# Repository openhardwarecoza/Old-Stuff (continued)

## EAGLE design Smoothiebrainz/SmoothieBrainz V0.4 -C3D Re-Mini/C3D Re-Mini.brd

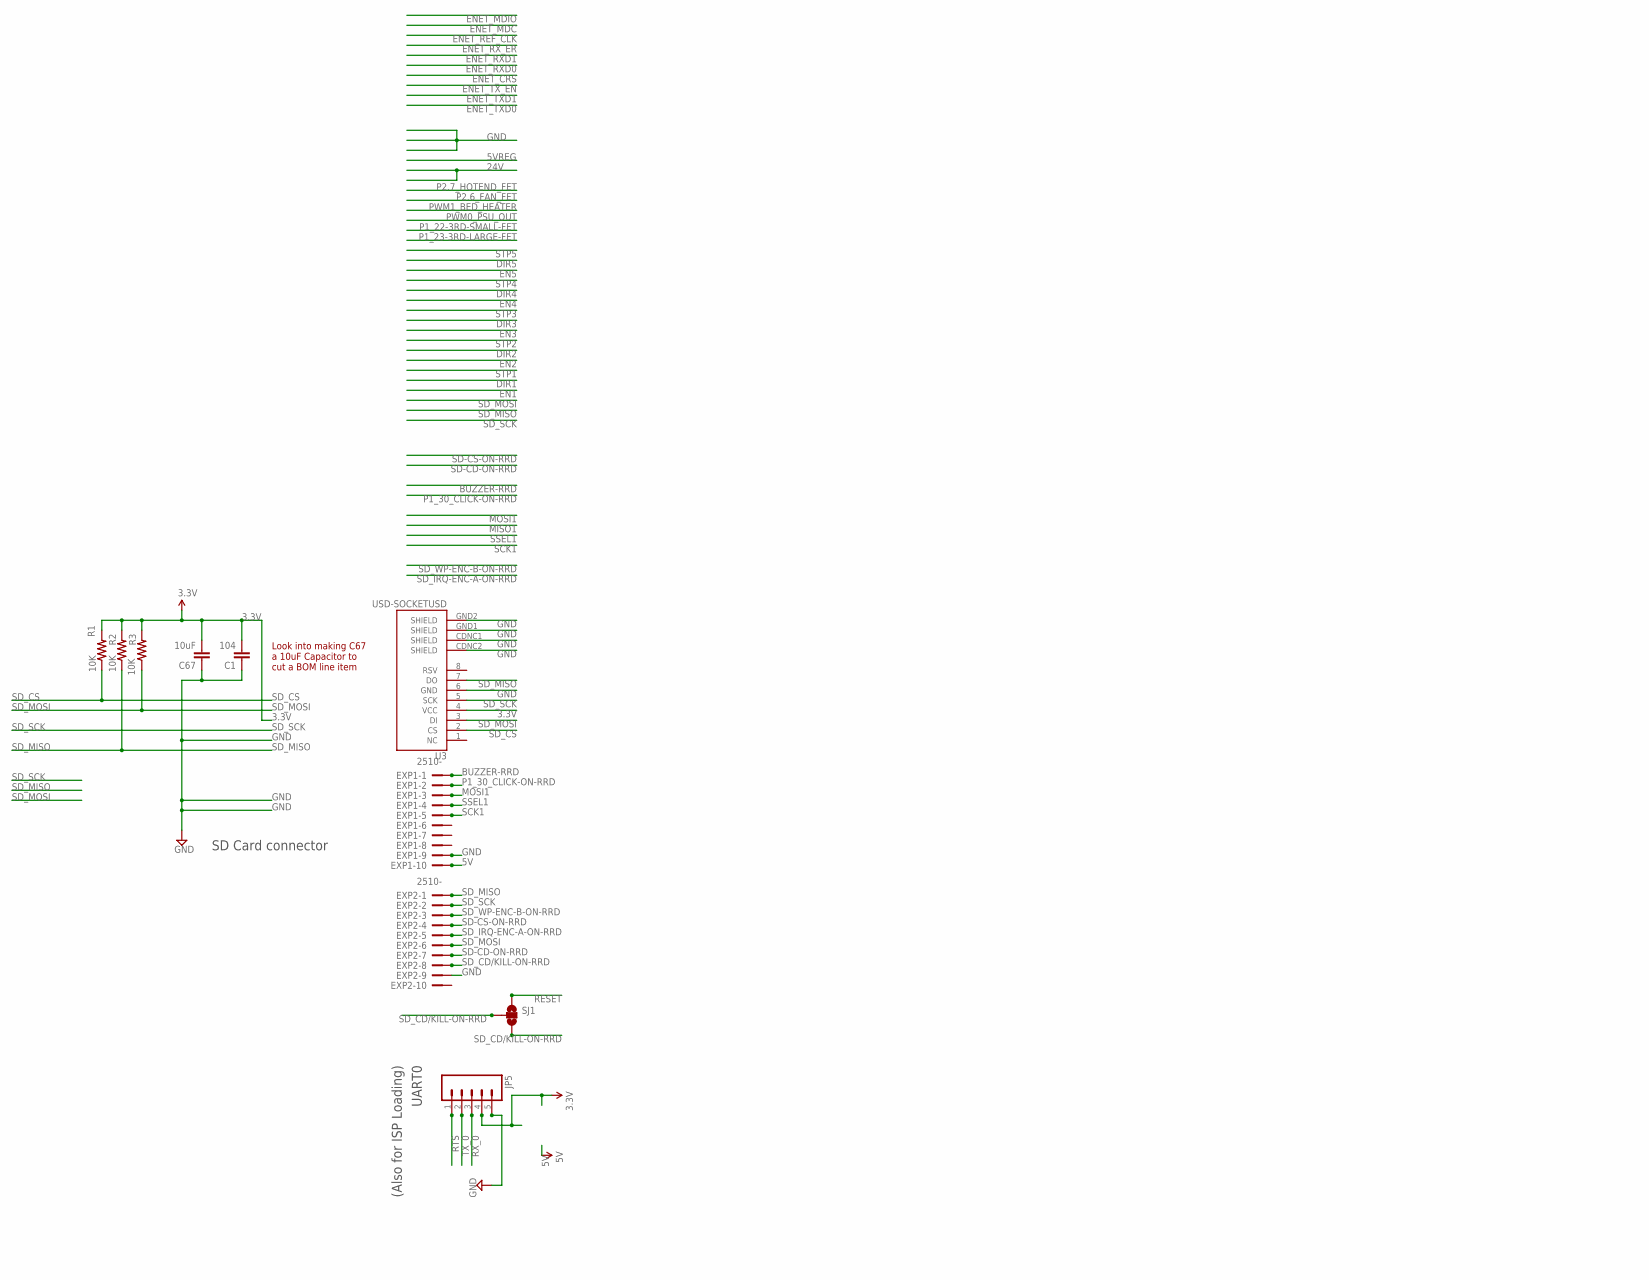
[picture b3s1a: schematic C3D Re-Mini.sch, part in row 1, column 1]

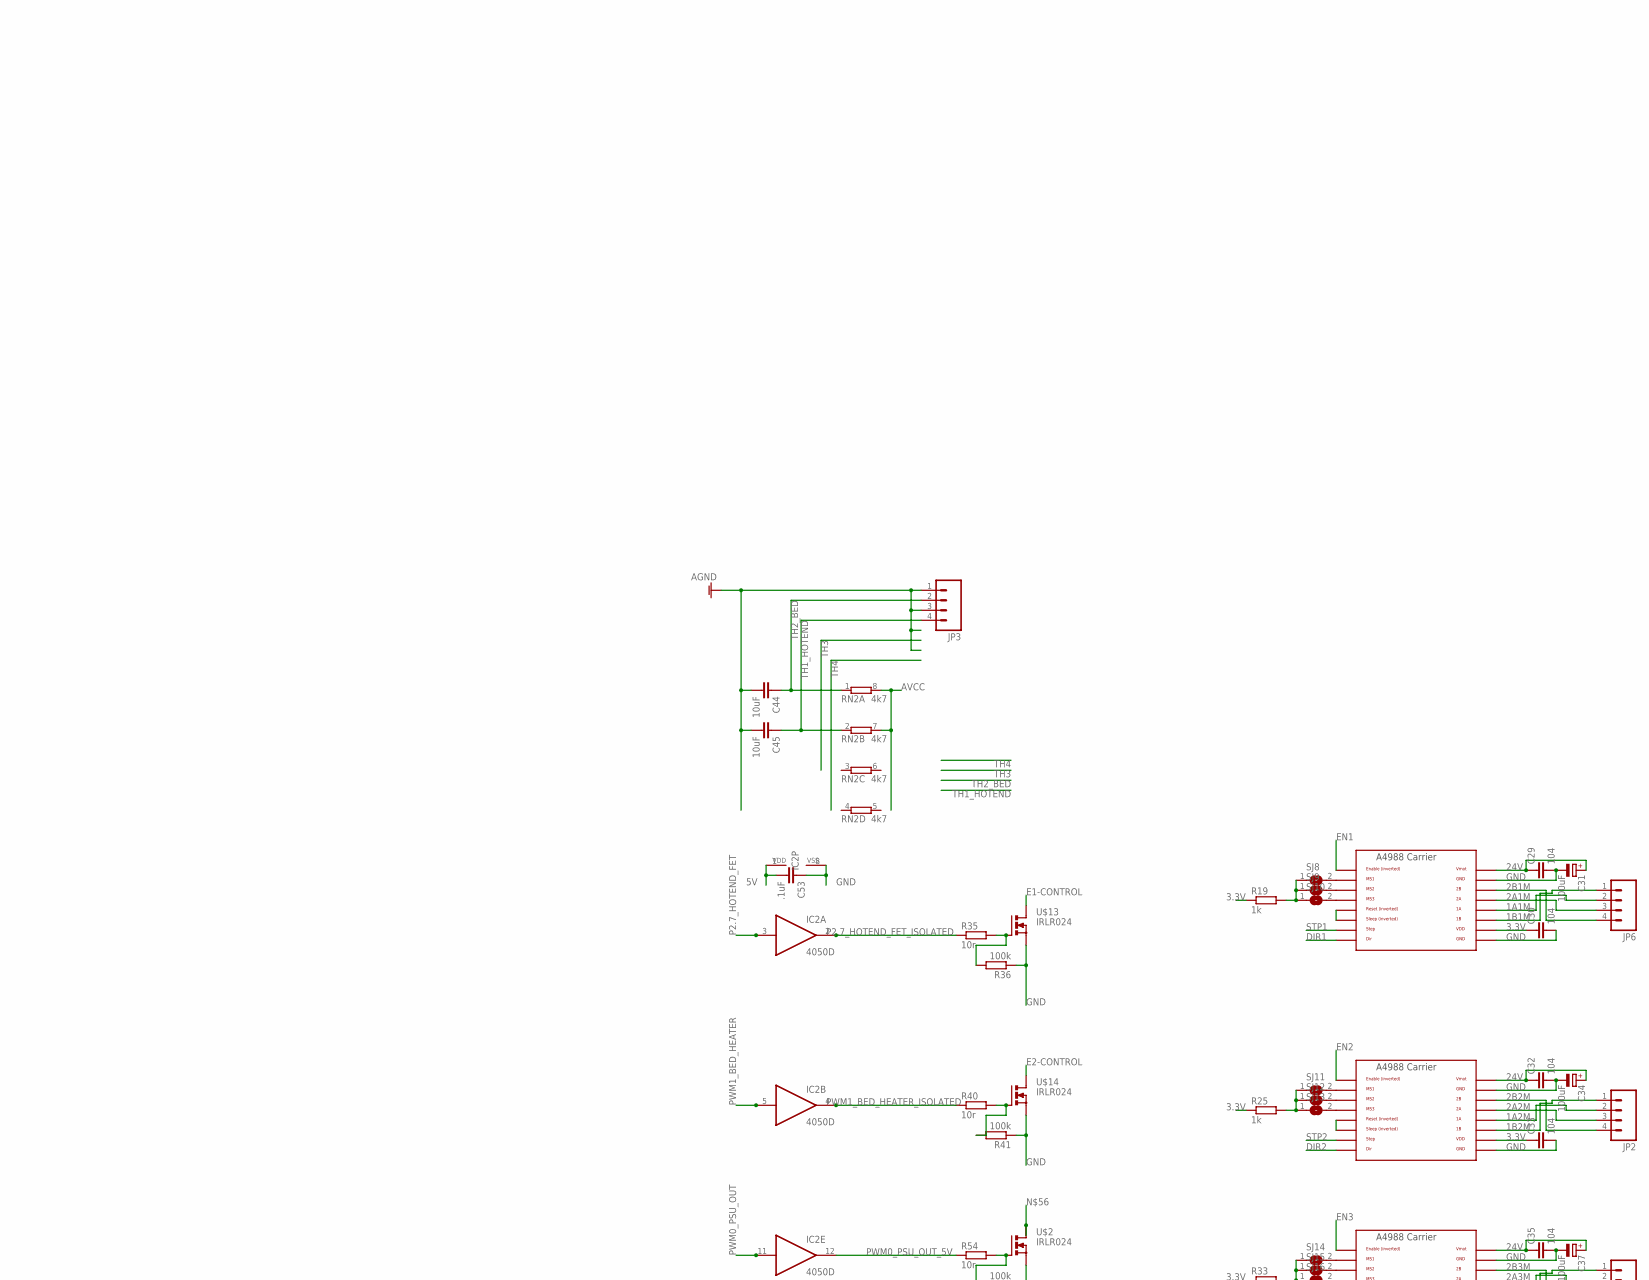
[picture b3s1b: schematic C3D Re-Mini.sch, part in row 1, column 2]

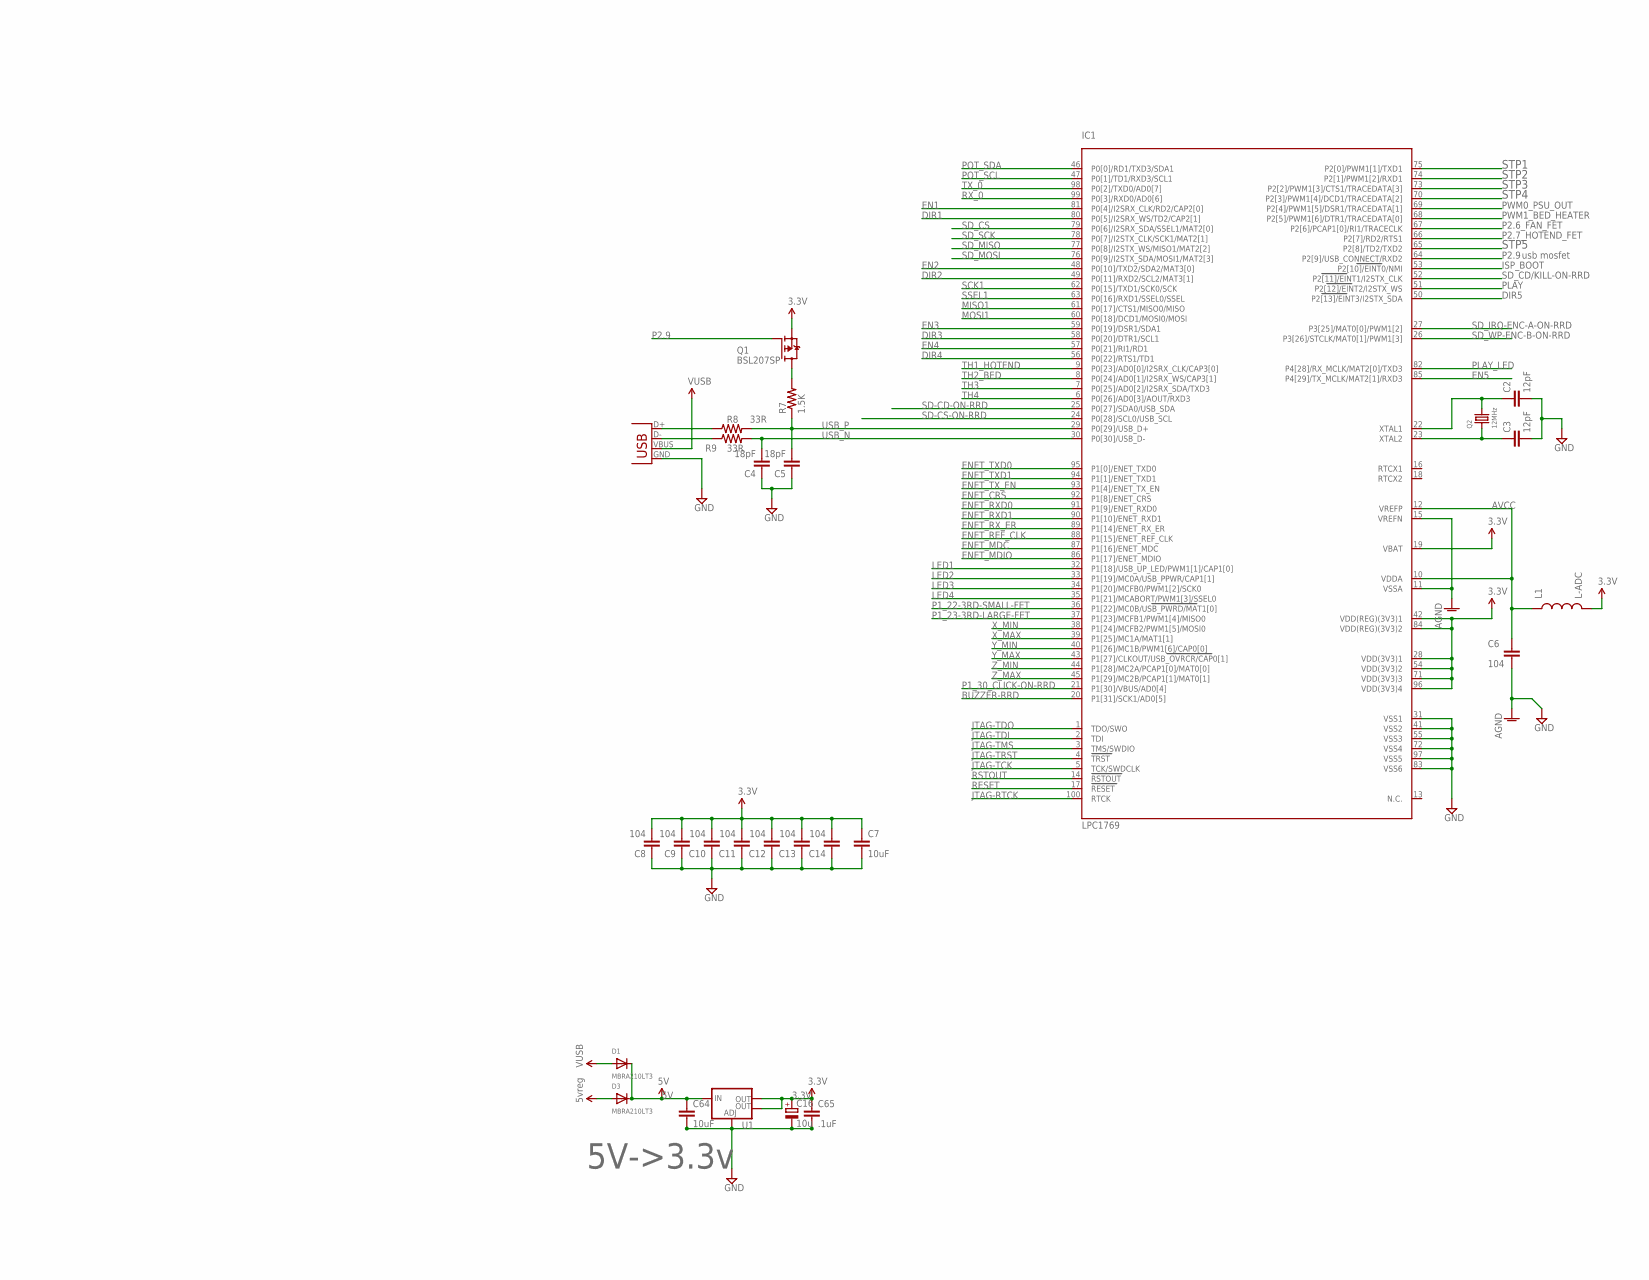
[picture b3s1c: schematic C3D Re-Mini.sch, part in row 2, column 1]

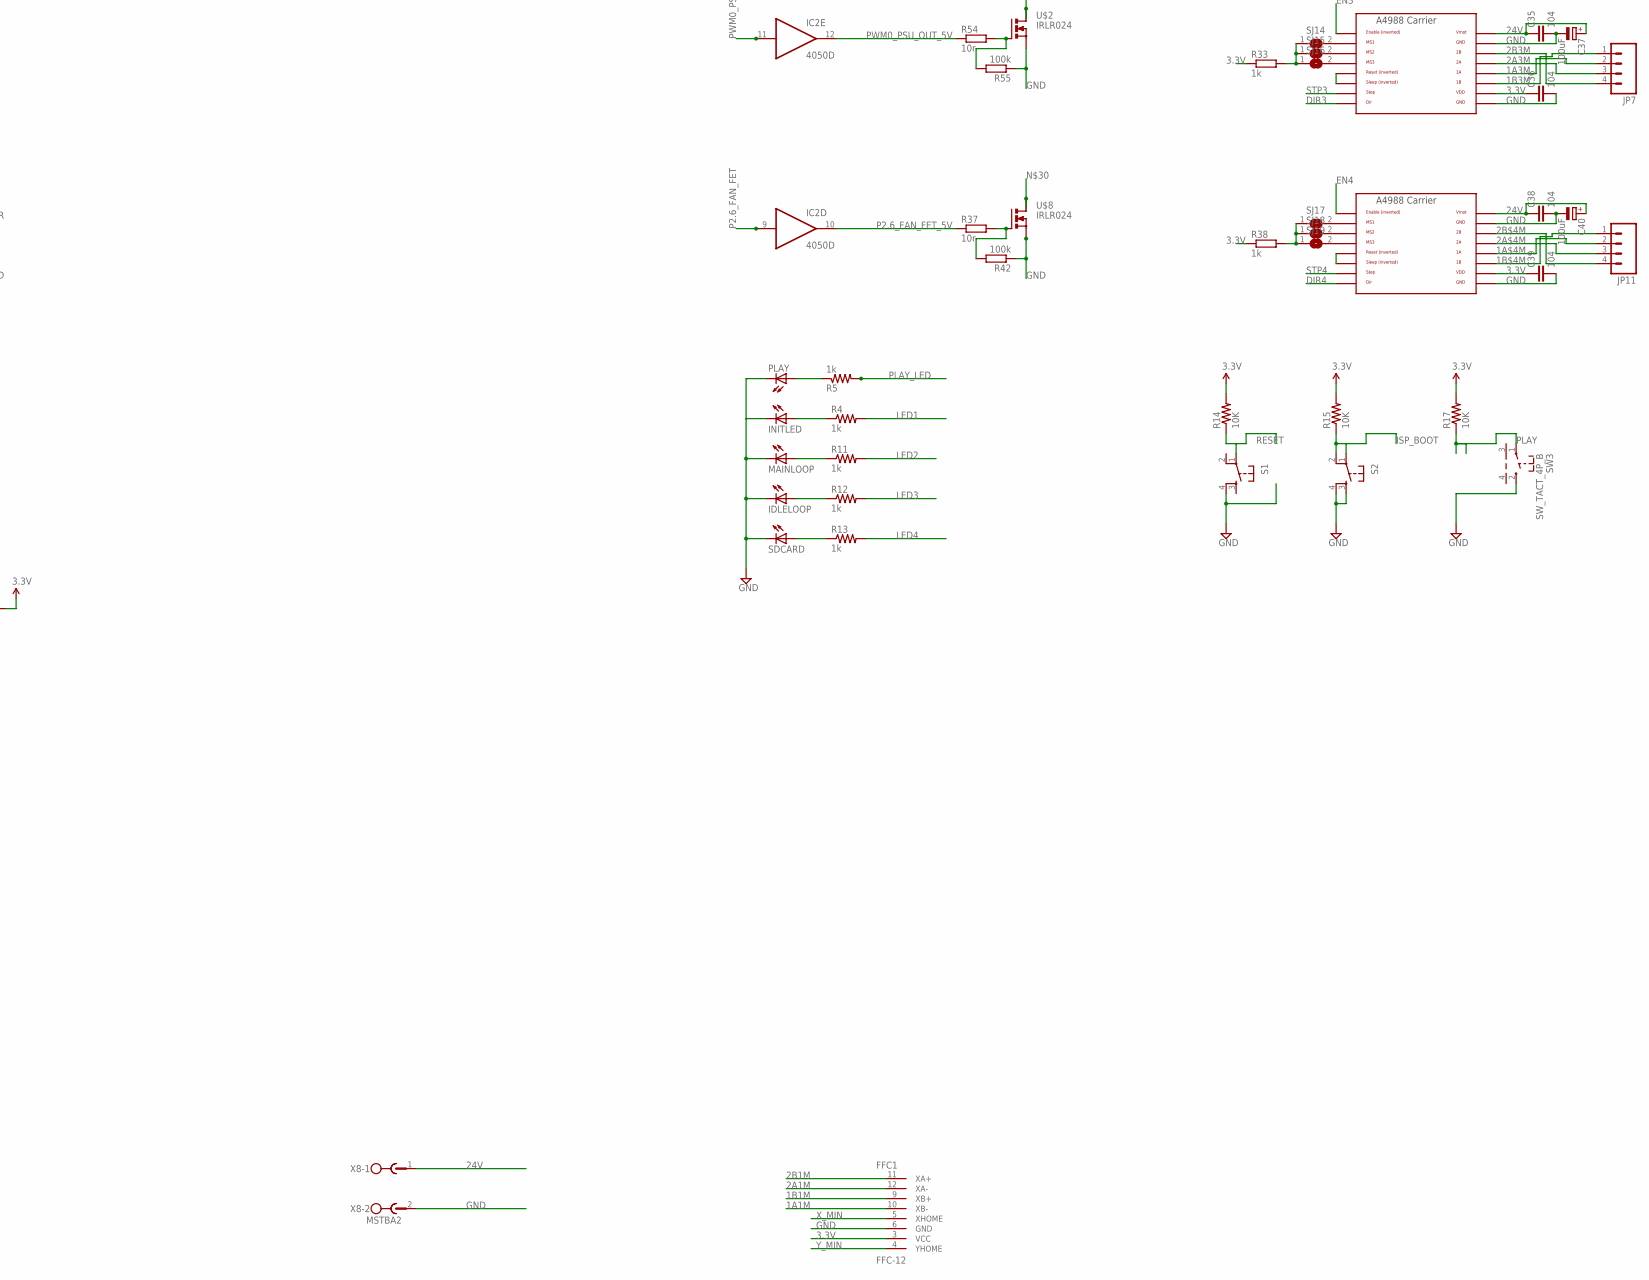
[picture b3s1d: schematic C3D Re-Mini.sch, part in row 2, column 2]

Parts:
C1, C6, C8, C9, C10, C11, C12, C13, C14, C29, C30, C32, C33, C35, C36, C38, C39: 104; C0603
C2, C3: 12pF; C0603
C4, C5: 18pF; C0603
C7, C44, C45, C67: 10uF; C0603
C16: 10u; E2-4
C31, C34, C37, C40: 100uF; 153CLV-0807
C53, C65: .1uF; C0603
C64: 10uF; C1206
D1, D3: MBRA210LT3; SMADIODE
EXP1, EXP2: 2510-; PAK100/2500-10
FFC1: FFC-12; FFC
IC1: LPC1769; LQFP100
IC2: 4050D; SO16
IDLELOOP: LEDCHIP-LED0805; CHIP-LED0805
INITLED: LEDCHIP-LED0805; CHIP-LED0805
JP2, JP6, JP7, JP11: M04POLAR_LOCK; MOLEX-1X4_LOCK
JP3: M04LOCK; 1X04_LOCK
JP5: M05NO_SILK; 1X05_NO_SILK
L1: L-ADC; 0603
MAINLOOP: LEDCHIP-LED0805; CHIP-LED0805
PLAY: LEDCHIP-LED0805; CHIP-LED0805
Q1: BSL207SP; SC74_INFINEON
Q2: 12MHz; CRYSTAL_3.2X2.5
R1, R2, R3, R14, R15, R17: 10K; R0603
R4, R5, R11, R12, R13: 1k; R0603
R7: 1.5K; R0603
R8, R9: 33R; R0603
R19, R25, R33, R38: 1k; R0603@1
R35, R37, R40, R54: 10r; R0603@1
R36, R41, R42, R55: 100k; R0603@1
RN2: 4k7; 0603-ARV
S1, S2: TAC_SWITCHSMD; TACTILE_SWITCH_SMD
SDCARD: LEDCHIP-LED0805; CHIP-LED0805
SJ1: SOLDERJUMPER_2WAYS; SJ_3
SJ8, SJ9, SJ10, SJ11, SJ12, SJ13, SJ14, SJ15, SJ16, SJ17, SJ18, SJ19: SJ
SW3: SW_TACT_4P_B; SW_TACT_STANDARD_RIGHT_ANGLE
U1: V_REG_LM1117SOT223; SOT223
U3: USD-SOCKETUSD; USD-SOCKET-PP
U$1, U$5, U$6, U$7: POLOLU_A4983CARRIER; A4988BREAKOUT
U$2, U$8, U$13, U$14: IRLR024; D-PAK_TO252AA
X8: MSTBA2
X14: USBPTH; USB-B-PTH

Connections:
1A1M: FFC1.10 (XB-), JP6.2, U$1.1A
1A2M: JP2.2, U$5.1A
1A3M: JP7.2, U$6.1A
1A$4M: JP11.2, U$7.1A
1B1M: FFC1.9 (XB+), JP6.1, U$1.1B
1B2M: JP2.1, U$5.1B
1B3M: JP7.1, U$6.1B
1B$4M: JP11.1, U$7.1B
2A1M: FFC1.12 (XA-), JP6.3, U$1.2A
2A2M: JP2.3, U$5.2A
2A3M: JP7.3, U$6.2A
2A$4M: JP11.3, U$7.2A
2B1M: FFC1.11 (XA+), JP6.4, U$1.2B
2B2M: JP2.4, U$5.2B
2B3M: JP7.4, U$6.2B
2B$4M: JP11.4, U$7.2B
3.3V: C1.2, C7.1, C8.2, C9.2, C10.2, C11.2, C12.2, C13.2, C14.2, C16.+, C30.1, C33.1, C36.1, C39.1, C65.1, C67.2, FFC1.3 (VCC), IC1.19 (VBAT), IC1.28 (VDD(3V3)1), IC1.42 (VDD(REG)(3V3)1), IC1.54 (VDD(3V3)2), IC1.71 (VDD(3V3)3), IC1.84 (VDD(REG)(3V3)2), IC1.96 (VDD(3V3)4), JP5.4, L1.2, Q1.4 (S), R1.2, R2.2, R3.2, R14.2, R15.2, R17.2, R19.1, R25.1, R33.1, R38.1, U1.2 (OUT), U1.4 (OUT), U3.4 (VCC), U$1.VDD, U$5.VDD, U$6.VDD, U$7.VDD
5V: C53.2, C64.1, D1.C, D3.C, EXP1.10, IC2.1 (VDD), U1.3 (IN)
5VREG: D3.A
24V: C29.1, C31.+, C32.1, C34.+, C35.1, C37.+, C38.1, C40.+, U$1.VMOT, U$5.VMOT, U$6.VMOT, U$7.VMOT, X8.1
AGND: C6.2, C44.2, C45.2, IC1.11 (VSSA), IC1.15 (VREFN), JP3.1, JP3.3
AVCC: C6.1, IC1.10 (VDDA), IC1.12 (VREFP), L1.1, RN2.7 (2), RN2.8 (2)
BUZZER-RRD: EXP1.1, IC1.20 (P1[31]/SCK1/AD0[5])
DIR1: IC1.80 (P0[5]/I2SRX_WS/TD2/CAP2[1]), U$1.DIR
DIR2: IC1.49 (P0[11]/RXD2/SCL2/MAT3[1]), U$5.DIR
DIR3: IC1.58 (P0[20]/DTR1/SCL1), U$6.DIR
DIR4: IC1.56 (P0[22]/RTS1/TD1), U$7.DIR
DIR5: IC1.50 (P2[13]/EINT3/I2STX_SDA)
E1-CONTROL: U$13.4 (D)
E2-CONTROL: U$14.4 (D)
EN1: IC1.81 (P0[4]/I2SRX_CLK/RD2/CAP2[0]), U$1.EN
EN2: IC1.48 (P0[10]/TXD2/SDA2/MAT3[0]), U$5.EN
EN3: IC1.59 (P0[19]/DSR1/SDA1), U$6.EN
EN4: IC1.57 (P0[21]/RI1/RD1), U$7.EN
EN5: IC1.85 (P4[29]/TX_MCLK/MAT2[1]/RXD3)
ENET_CRS: IC1.92 (P1[8]/ENET_CRS)
ENET_MDC: IC1.87 (P1[16]/ENET_MDC)
ENET_MDIO: IC1.86 (P1[17]/ENET_MDIO)
ENET_REF_CLK: IC1.88 (P1[15]/ENET_REF_CLK)
ENET_RXD0: IC1.91 (P1[9]/ENET_RXD0)
ENET_RXD1: IC1.90 (P1[10]/ENET_RXD1)
ENET_RX_ER: IC1.89 (P1[14]/ENET_RX_ER)
ENET_TXD0: IC1.95 (P1[0]/ENET_TXD0)
ENET_TXD1: IC1.94 (P1[1]/ENET_TXD1)
ENET_TX_EN: IC1.93 (P1[4]/ENET_TX_EN)
GND: C1.1, C2.2, C3.2, C4.1, C5.1, C7.2, C8.1, C9.1, C10.1, C11.1, C12.1, C13.1, C14.1, C16.-, C29.2, C30.2, C31.-, C32.2, C33.2, C34.-, C35.2, C36.2, C37.-, C38.2, C39.2, C40.-, C53.1, C64.2, C65.2, C67.1, EXP1.9, EXP2.9, FFC1.6 (GND), IC1.31 (VSS1), IC1.41 (VSS2), IC1.55 (VSS3), IC1.72 (VSS4), IC1.83 (VSS6), IC1.97 (VSS5), IC2.8 (VSS), IDLELOOP.C, INITLED.C, JP5.5, MAINLOOP.C, PLAY.C, R36.1, R41.1, R42.1, R55.1, S1.4, S2.3, S2.4, SDCARD.C, SW3.2, U1.1 (ADJ), U3.6 (GND), U3.CDNC1 (SHIELD), U3.CDNC2 (SHIELD), U3.GND1 (SHIELD), U3.GND2 (SHIELD), U$1.GND, U$1.GND@0 (GND), U$2.3 (S), U$5.GND, U$5.GND@0 (GND), U$6.GND, U$6.GND@0 (GND), U$7.GND, U$7.GND@0 (GND), U$8.3 (S), U$13.3 (S), U$14.3 (S), X8.2, X14.GND
ISP_BOOT: IC1.53 (P2[10]/EINT0/NMI), R15.1, S2.1, S2.2
JTAG-RTCK: IC1.100 (RTCK)
JTAG-TCK: IC1.5 (TCK/SWDCLK)
JTAG-TDI: IC1.2 (TDI)
JTAG-TDO: IC1.1 (TDO/SWO)
JTAG-TMS: IC1.3 (TMS/SWDIO)
JTAG-TRST: IC1.4 (TRST)
LED1: IC1.32 (P1[18]/USB_UP_LED/PWM1[1]/CAP1[0]), R4.2
LED2: IC1.33 (P1[19]/MC0A/USB_PPWR/CAP1[1]), R11.2
LED3: IC1.34 (P1[20]/MCFB0/PWM1[2]/SCK0), R12.2
LED4: IC1.35 (P1[21]/MCABORT/PWM1[3]/SSEL0), R13.2
MISO1: IC1.61 (P0[17]/CTS1/MISO0/MISO)
MOSI1: EXP1.3, IC1.60 (P0[18]/DCD1/MOSI0/MOSI)
unnamed: C2.1, IC1.22 (XTAL1), Q2.2
unnamed: C3.1, IC1.23 (XTAL2), Q2.1
unnamed: PLAY.A, R5.1
unnamed: SJ8.2, U$1.MS1
unnamed: SJ9.2, U$1.MS2
unnamed: SJ10.2, U$1.MS3
unnamed: U$5.RST, U$5.SLP (SLEEP)
unnamed: R25.2, SJ11.1, SJ12.1, SJ13.1
unnamed: SJ11.2, U$5.MS1
unnamed: SJ12.2, U$5.MS2
unnamed: SJ13.2, U$5.MS3
unnamed: U$6.RST, U$6.SLP (SLEEP)
unnamed: R37.2, R42.2, U$8.1 (G)
unnamed: R33.2, SJ14.1, SJ15.1, SJ16.1
unnamed: SJ14.2, U$6.MS1
unnamed: SJ15.2, U$6.MS2
unnamed: SJ16.2, U$6.MS3
unnamed: R35.2, R36.2, U$13.1 (G)
unnamed: R19.2, SJ8.1, SJ9.1, SJ10.1
unnamed: U$7.RST, U$7.SLP (SLEEP)
unnamed: R38.2, SJ17.1, SJ18.1, SJ19.1
unnamed: SJ17.2, U$7.MS1
unnamed: SJ18.2, U$7.MS2
unnamed: U$1.RST, U$1.SLP (SLEEP)
unnamed: SJ19.2, U$7.MS3
unnamed: R40.2, R41.2, U$14.1 (G)
unnamed: Q1.1 (D), Q1.2 (D), Q1.5 (D), Q1.6 (D), R7.2
unnamed: R54.2, R55.2, U$2.1 (G)
unnamed: R8.1, X14.D+
unnamed: R9.1, X14.D-
unnamed: R13.1, SDCARD.A
unnamed: IDLELOOP.A, R12.1
unnamed: MAINLOOP.A, R11.1
unnamed: INITLED.A, R4.1
P1_22-3RD-SMALL-FET: IC1.36 (P1[22]/MC0B/USB_PWRD/MAT1[0])
P1_23-3RD-LARGE-FET: IC1.37 (P1[23]/MCFB1/PWM1[4]/MISO0)
P1_30_CLICK-ON-RRD: EXP1.2, IC1.21 (P1[30]/VBUS/AD0[4])
P2.6_FAN_FET: IC1.67 (P2[6]/PCAP1[0]/RI1/TRACECLK), IC2.9 (I)
P2.6_FAN_FET_5V: IC2.10 (O), R37.1
P2.7_HOTEND_FET: IC1.66 (P2[7]/RD2/RTS1), IC2.3 (I)
P2.7_HOTEND_FET_ISOLATED: IC2.2 (O), R35.1
P2.9: IC1.64 (P2[9]/USB_CONNECT/RXD2), Q1.3 (G)
PLAY: IC1.51 (P2[12]/EINT2/I2STX_WS), R17.1, SW3.1
PLAY_LED: IC1.82 (P4[28]/RX_MCLK/MAT2[0]/TXD3), R5.2
POT_SCL: IC1.47 (P0[1]/TD1/RXD3/SCL1)
POT_SDA: IC1.46 (P0[0]/RD1/TXD3/SDA1)
PWM0_PSU_OUT: IC1.69 (P2[4]/PWM1[5]/DSR1/TRACEDATA[1]), IC2.11 (I)
PWM0_PSU_OUT_5V: IC2.12 (O), R54.1
PWM1_BED_HEATER: IC1.68 (P2[5]/PWM1[6]/DTR1/TRACEDATA[0]), IC2.5 (I)
PWM1_BED_HEATER_ISOLATED: IC2.4 (O), R40.1
RESET: IC1.17 (RESET), R14.1, S1.1, SJ1.1
RSTOUT: IC1.14 (RSTOUT)
RTS: JP5.1
RX_0: IC1.99 (P0[3]/RXD0/AD0[6]), JP5.3
SCK1: EXP1.5, IC1.62 (P0[15]/TXD1/SCK0/SCK)
SD-CD-ON-RRD: EXP2.7, IC1.25 (P0[27]/SDA0/USB_SDA)
SD-CS-ON-RRD: EXP2.4, IC1.24 (P0[28]/SCL0/USB_SCL)
SD_CD/KILL-ON-RRD: EXP2.8, IC1.52 (P2[11]/EINT1/I2STX_CLK), SJ1.2, SJ1.3
SD_CS: IC1.79 (P0[6]/I2SRX_SDA/SSEL1/MAT2[0]), R1.1, U3.2 (CS)
SD_IRQ-ENC-A-ON-RRD: EXP2.5, IC1.27 (P3[25]/MAT0[0]/PWM1[2])
SD_MISO: EXP2.1, IC1.77 (P0[8]/I2STX_WS/MISO1/MAT2[2]), R2.1, U3.7 (DO)
SD_MOSI: EXP2.6, IC1.76 (P0[9]/I2STX_SDA/MOSI1/MAT2[3]), R3.1, U3.3 (DI)
SD_SCK: EXP2.2, IC1.78 (P0[7]/I2STX_CLK/SCK1/MAT2[1]), U3.5 (SCK)
SD_WP-ENC-B-ON-RRD: EXP2.3, IC1.26 (P3[26]/STCLK/MAT0[1]/PWM1[3])
SSEL1: EXP1.4, IC1.63 (P0[16]/RXD1/SSEL0/SSEL)
STP1: IC1.75 (P2[0]/PWM1[1]/TXD1), U$1.STEP
STP2: IC1.74 (P2[1]/PWM1[2]/RXD1), U$5.STEP
STP3: IC1.73 (P2[2]/PWM1[3]/CTS1/TRACEDATA[3]), U$6.STEP
STP4: IC1.70 (P2[3]/PWM1[4]/DCD1/TRACEDATA[2]), U$7.STEP
STP5: IC1.65 (P2[8]/TD2/TXD2)
TH1_HOTEND: C45.1, IC1.9 (P0[23]/AD0[0]/I2SRX_CLK/CAP3[0]), JP3.4, RN2.2 (1)
TH2_BED: C44.1, IC1.8 (P0[24]/AD0[1]/I2SRX_WS/CAP3[1]), JP3.2, RN2.1
TH3: IC1.7 (P0[25]/AD0[2]/I2SRX_SDA/TXD3)
TH4: IC1.6 (P0[26]/AD0[3]/AOUT/RXD3)
TX_0: IC1.98 (P0[2]/TXD0/AD0[7]), JP5.2
USB_N: C4.2, IC1.30 (P0[30]/USB_D-), R9.2
USB_P: C5.2, IC1.29 (P0[29]/USB_D+), R7.1, R8.2
VUSB: D1.A, X14.VBUS
X_MAX: IC1.39 (P1[25]/MC1A/MAT1[1])
X_MIN: FFC1.5 (XHOME), IC1.38 (P1[24]/MCFB2/PWM1[5]/MOSI0)
Y_MAX: IC1.43 (P1[27]/CLKOUT/USB_OVRCR/CAP0[1])
Y_MIN: FFC1.4 (YHOME), IC1.40 (P1[26]/MC1B/PWM1[6]/CAP0[0])
Z_MAX: IC1.45 (P1[29]/MC2B/PCAP1[1]/MAT0[1])
Z_MIN: IC1.44 (P1[28]/MC2A/PCAP1[0]/MAT0[0])

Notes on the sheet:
SD Card connector
UART0
(Also for ISP Loading)
usb mosfet
5V->3.3v
Look into making C67 a 10uF Capacitor to cut a BOM line item

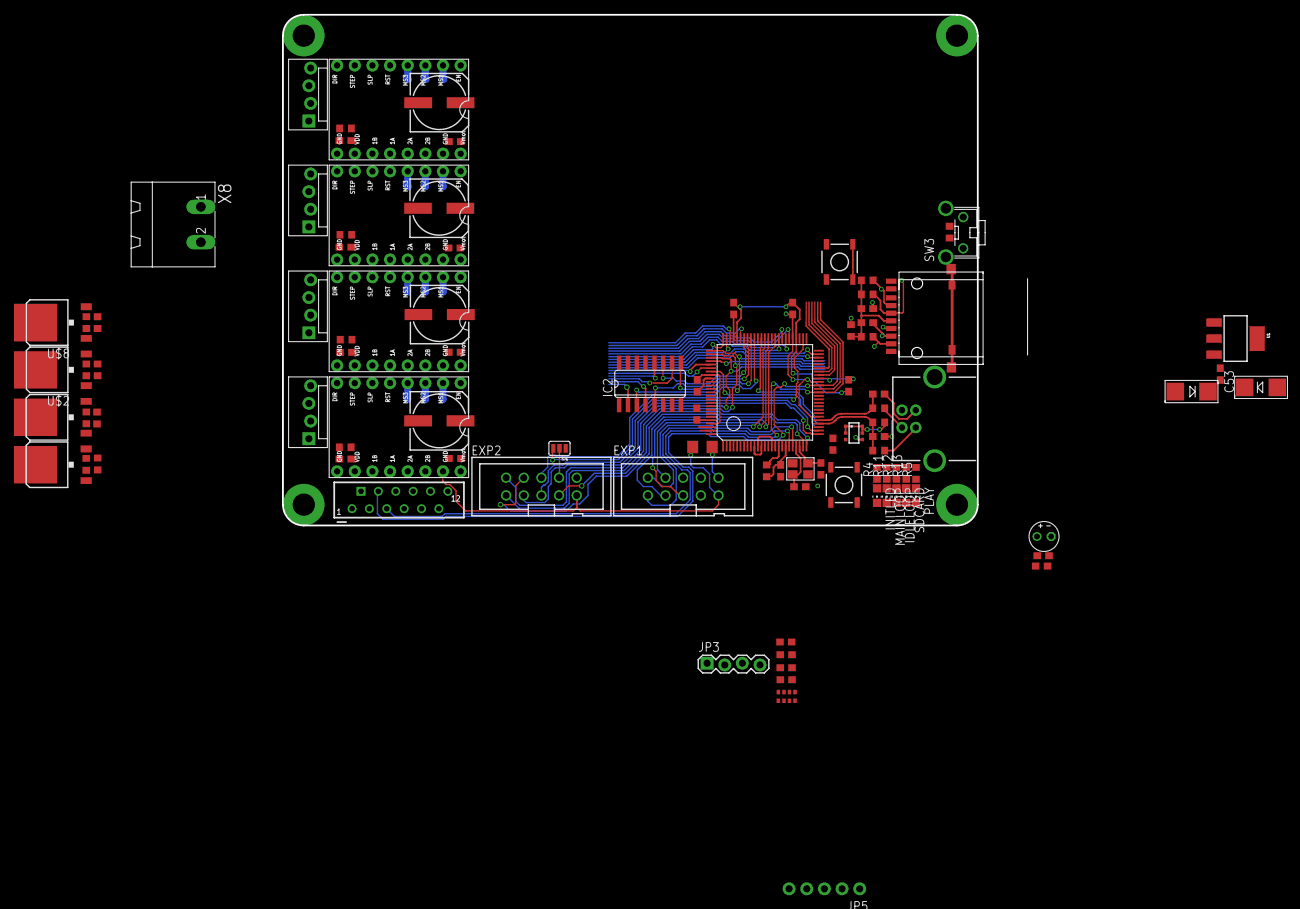
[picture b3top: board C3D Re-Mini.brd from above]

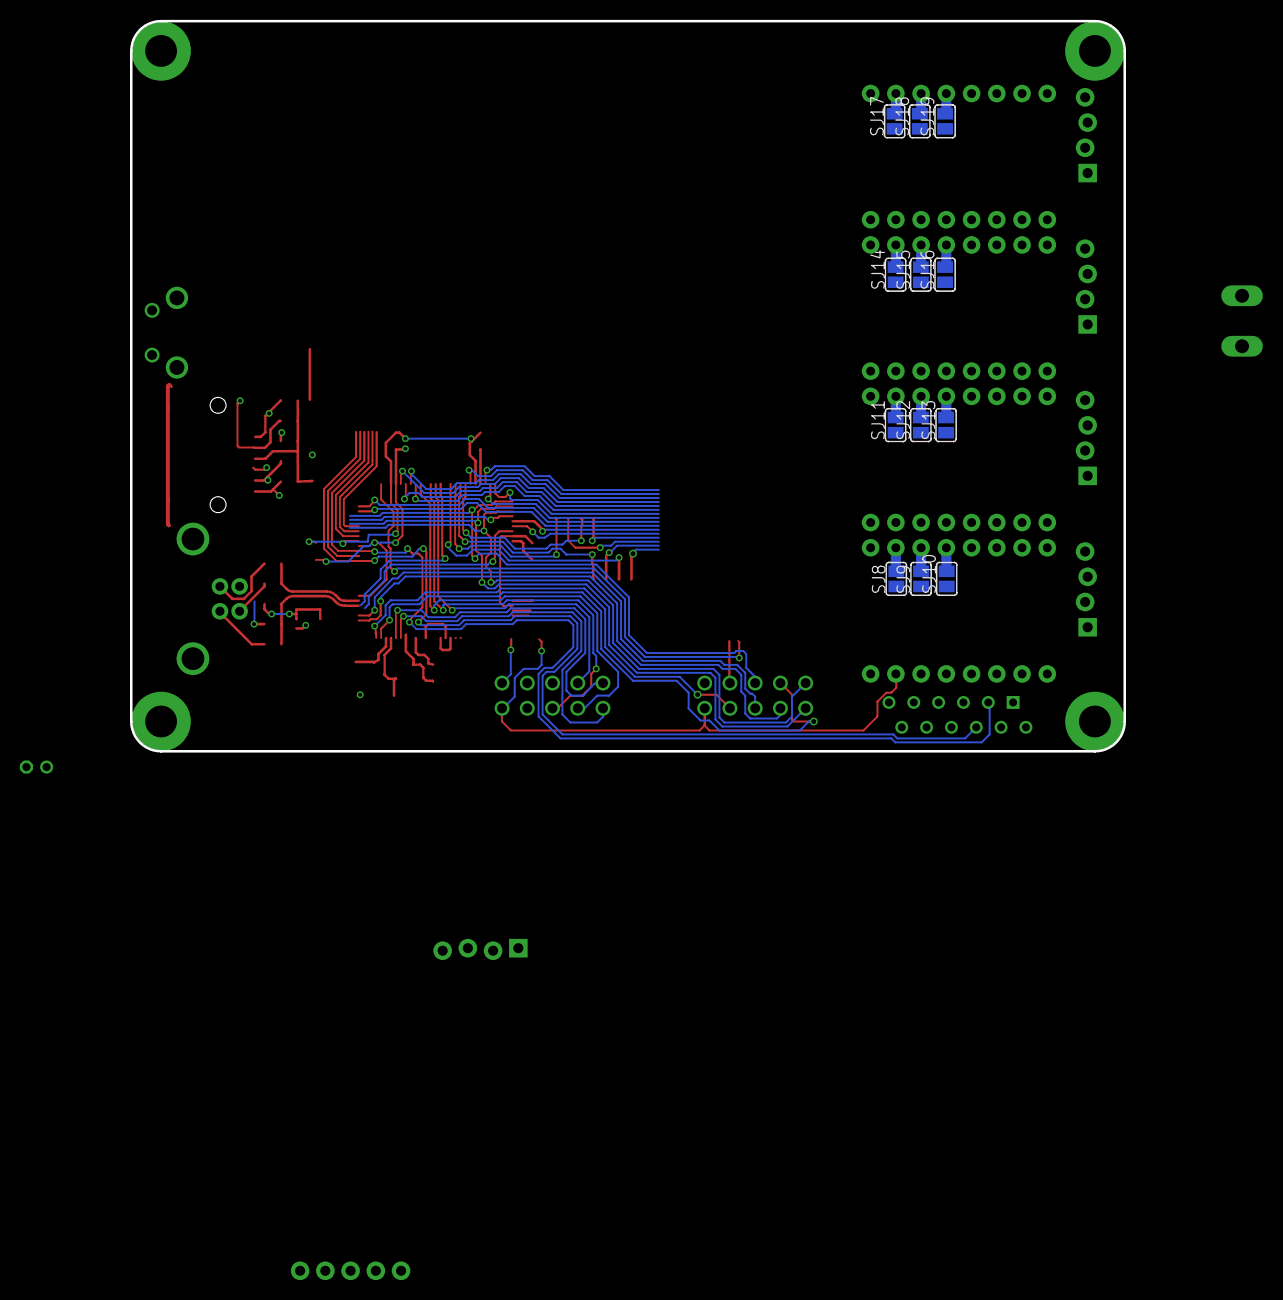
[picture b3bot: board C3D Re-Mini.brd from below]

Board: 2 copper layers, 100.0 x 73.5 mm, 109 parts (12 on the bottom side), 108 nets.

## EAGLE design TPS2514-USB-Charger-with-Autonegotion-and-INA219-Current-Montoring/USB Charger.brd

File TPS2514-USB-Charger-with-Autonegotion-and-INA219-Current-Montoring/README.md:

# TPS2514-USB-Charger-with-Autonegotion-and-INA219-Current-Montoring

TI TPS2514 is used to automatically negotaite max USB charge current to attached device

Second port has the famous Adafruit Mintyboost USB resistors to also try fooling device into max charge current.

With my Samsung S5 I get 1200mAh charge rate on the resistors, and 1700mAh on the TPS2514 Port

Also onboard is an INA219 voltage/current over I2C monitor and a LM2596 3A stepdowm converter (So plug 12-30v in, get 5v out, but also a negotiated charge for maximum charging current)

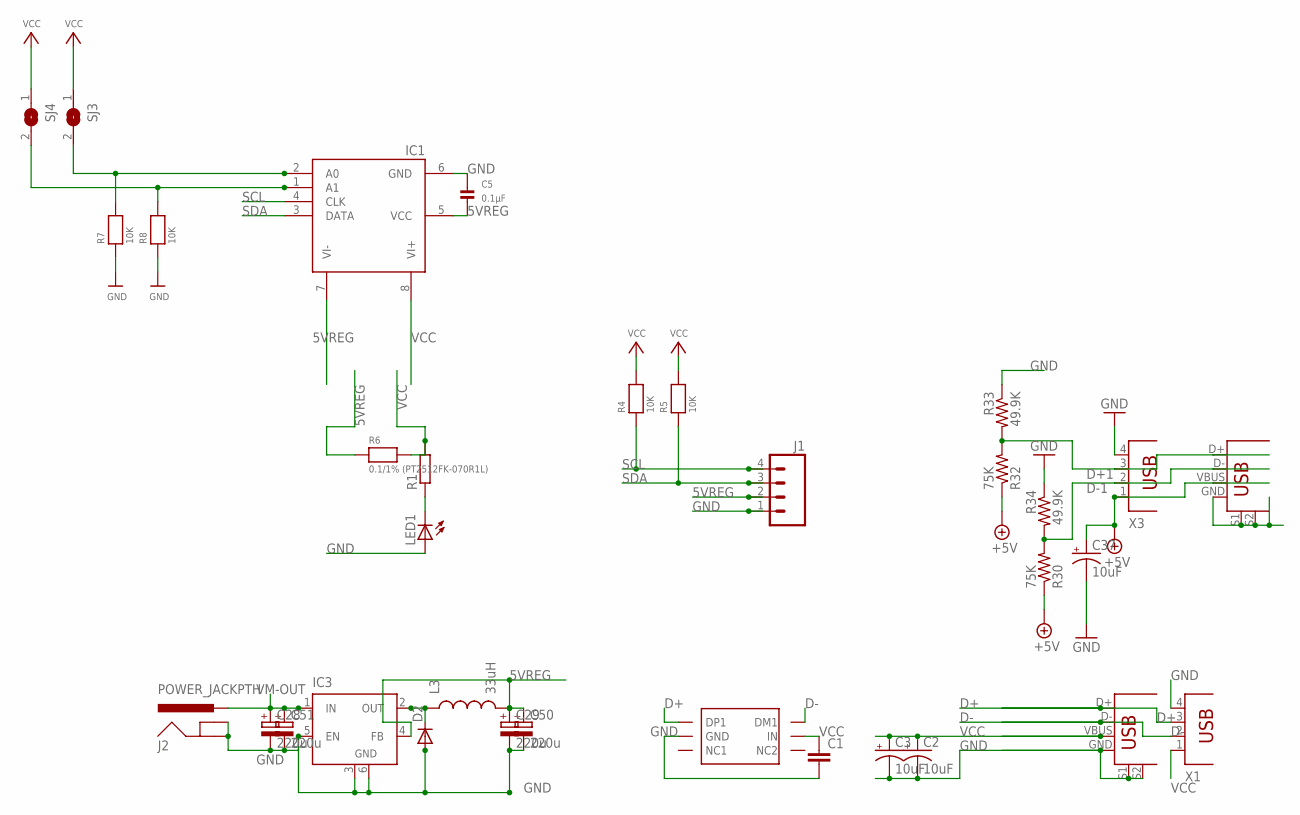
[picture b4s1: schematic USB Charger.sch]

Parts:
C1: C-EUC1206; C1206
C2, C3, C37: 10uF; EIA3216
C5: 0.1µF; 1206
C28, C29: 220u; E2,5-7
C50, C51: 220u; PANASONIC_D
D2: DIODE-DO-214AC; DO-214AC
IC1: INA219D; SO08
IC3: LM2596S; TO263-5
J1: M04POLAR_LOCK; MOLEX-1X4_LOCK
J2: POWER_JACKPTH; POWER_JACK_PTH
L3: 33uH; CDRH125
LED1: LED5MM
R1: R-EU_M1206; M1206
R4, R5, R7, R8: 10K; 1206
R6: 0.1/1% (PT2512FK-070R1L); 2512
R30, R32: 75K; M1206
R33, R34: 49.9K; M1206
SJ3, SJ4: SOLDERJUMPERREFLOW_NOPASTE; SOLDERJUMPER_REFLOW_NOPASTE
U$1: TPS2514
U$2, U$3: USB+SHIELDUSB-A-S-NOSILK-FEMALE; USB-A-S-NOSILK-FEMALE
X1, X3: PN87520

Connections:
5VREG: C5.2, C29.+, C50.+, IC1.5 (VCC), IC1.7 (VI-), IC3.4 (FB), J1.2, L3.2, R4.2, R5.2, R6.1
D+: U$1.DP1, U$2.D+, X1.3
D+1: R32.2, R33.2, U$3.D+, X3.3
D-: U$1.DM1, U$2.D-, X1.2
D-1: R30.2, R34.2, U$3.D-, X3.2
GND: C1.2, C2.C (-), C3.C (-), C5.1, C28.-, C29.-, C37.C (-), C50.-, C51.-, D2.2 (A), IC1.6 (GND), IC3.3 (GND), IC3.5 (EN), IC3.6 (GND), J1.1, J2.GND, J2.GNDBREAK, LED1.A, R7.1, R8.1, R33.1, R34.1, U$1.GND, U$2.GND, U$2.S1, U$2.S2, U$3.GND, U$3.S1, U$3.S2, X1.4, X3.4
unnamed: LED1.K (C), R1.1
unnamed: IC1.1 (A1), R8.2, SJ4.2
unnamed: IC1.2 (A0), R7.2, SJ3.2
unnamed: D2.1 (C), IC3.2 (OUT), L3.1
SCL: IC1.4 (CLK), J1.4, R4.1
SDA: IC1.3 (DATA), J1.3, R5.1
VCC: C1.1, C2.A (+), C3.A (+), C37.A (+), IC1.8 (VI+), R1.2, R6.2, R30.1, R32.1, SJ3.1, SJ4.1, U$1.IN, U$2.VBUS, U$3.VBUS, X1.1, X3.1
VM-OUT: C28.+, C51.+, IC3.1 (IN), J2.PWR

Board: 2 copper layers, 33 parts (0 on the bottom side), 14 nets, no tracks yet.
